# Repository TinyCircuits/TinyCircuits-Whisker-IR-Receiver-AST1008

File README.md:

# TinyCircuits Wireling IR Receiver
# AST1008 Rev1

The design files are located under design_files/ for the TinyCircuits AST1008 Rev 1 PCB. This is a Wireling board which features the Vishay TSOP57438 IR receiver optimized for Infrared signals near 38kHz. This sensor is most sensitive to the 950nm wavelength, outputs a demodulated data signal. (Pairs well with our IR Emitter Whisker)

Format is in Cadsoft Eagle format - Eagle version 6.2 was used for the original design.

For more infomation on this, check out the product page at TinyCircuits.com

# License:

Design by TinyCircuits.
All design files are released under the Creative Commons Attribution Share-Alike 3.0 License, see the following link for details: http://creativecommons.org/licenses/by-sa/3.0

All text above must be included in any redistribution or derived design

This project uses designs and concepts developed as part of the Arduino project and the LilyPad project.  The TinyCircuits design files themselves (schematics, PCB and libraries) are not directly derived from these works' design files and have been created new, however the concepts and basic architecture behind the TinyDuino and TinyLily products are derived and we thank the hard work of the organizations below for their contributions to open-source hardware:
  
Original Arduino Uno Design by Team Arduino

LilyPad Arduino Design by Leah Buechley and Sparkfun Electronics

Please support the open-source hardware community

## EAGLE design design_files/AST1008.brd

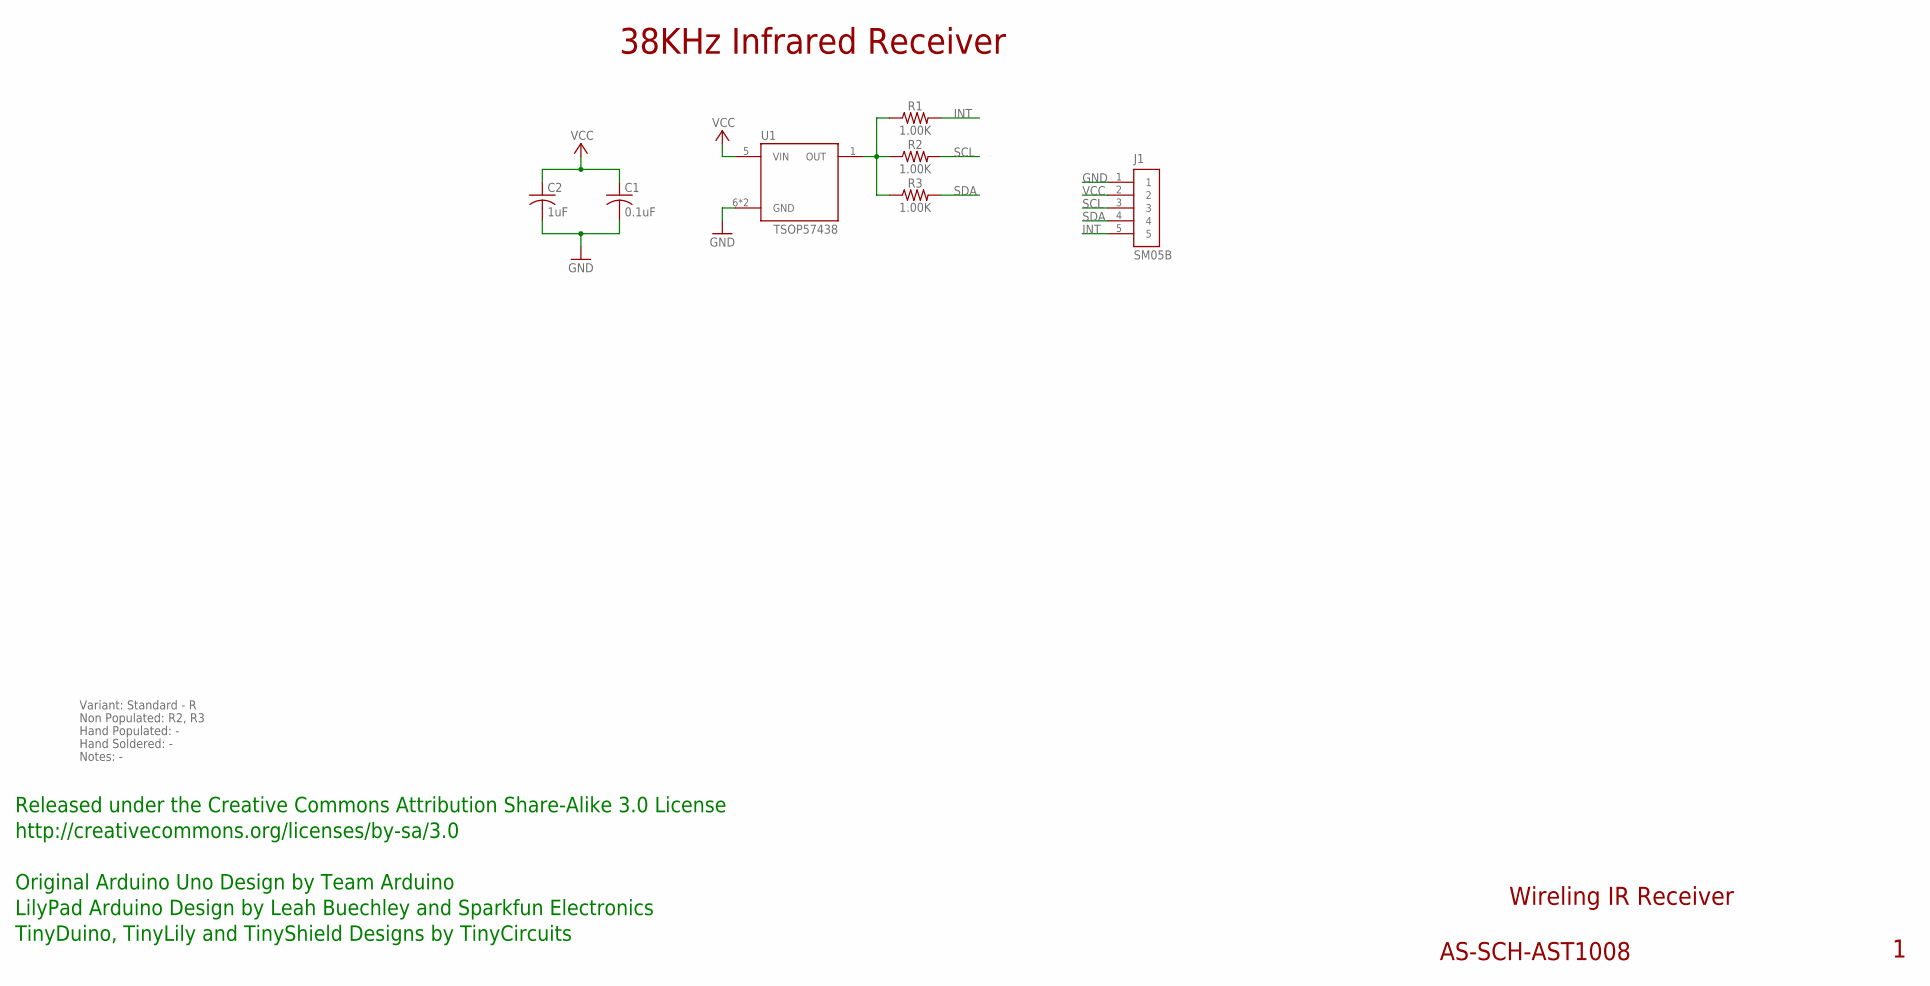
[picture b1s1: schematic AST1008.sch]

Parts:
C1: 0.1uF; C0402
C2: 1uF; C0603; PARTNO AS-ITM-00410
J1: SM05B; JST_SH_5X1_EDGE
R1, R2, R3: 1.00K; 0402; PARTNO AS-ITM-00003
U1: TSOP57438; TSOP57

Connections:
GND: C1.2, C2.2, J1.1, U1.6 (GND), U1.8 (GND)
GPIO1: R1.1, R2.1, R3.1, U1.1 (OUT)
INT: J1.5, R1.2
SCL: J1.3, R2.2
SDA: J1.4, R3.2
VCC: C1.1, C2.1, J1.2, U1.5 (VIN)

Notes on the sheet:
Wireling IR Receiver
AS-SCH-AST1008
38KHz Infrared Receiver
Released under the Creative Commons Attribution Share-Alike 3.0 License
http://creativecommons.org/licenses/by-sa/3.0
Original Arduino Uno Design by Team Arduino
TinyDuino, TinyLily and TinyShield Designs by TinyCircuits
LilyPad Arduino Design by Leah Buechley and Sparkfun Electronics
Non Populated: R2, R3
Hand Populated: -
Hand Soldered: -
Variant: Standard - R
Notes: -

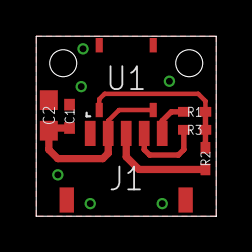
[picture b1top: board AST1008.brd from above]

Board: 2 copper layers, 10.0 x 10.0 mm, 8 parts (0 on the bottom side), 6 nets.

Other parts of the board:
U$1: DOCFIELD-TINYCIRCUITS-PCB

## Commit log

2019-08-02 added datasheet
2019-12-17 updated documentation
2020-02-04 mass image update
2020-05-12 updated code
2020-08-14 Add CAD data
